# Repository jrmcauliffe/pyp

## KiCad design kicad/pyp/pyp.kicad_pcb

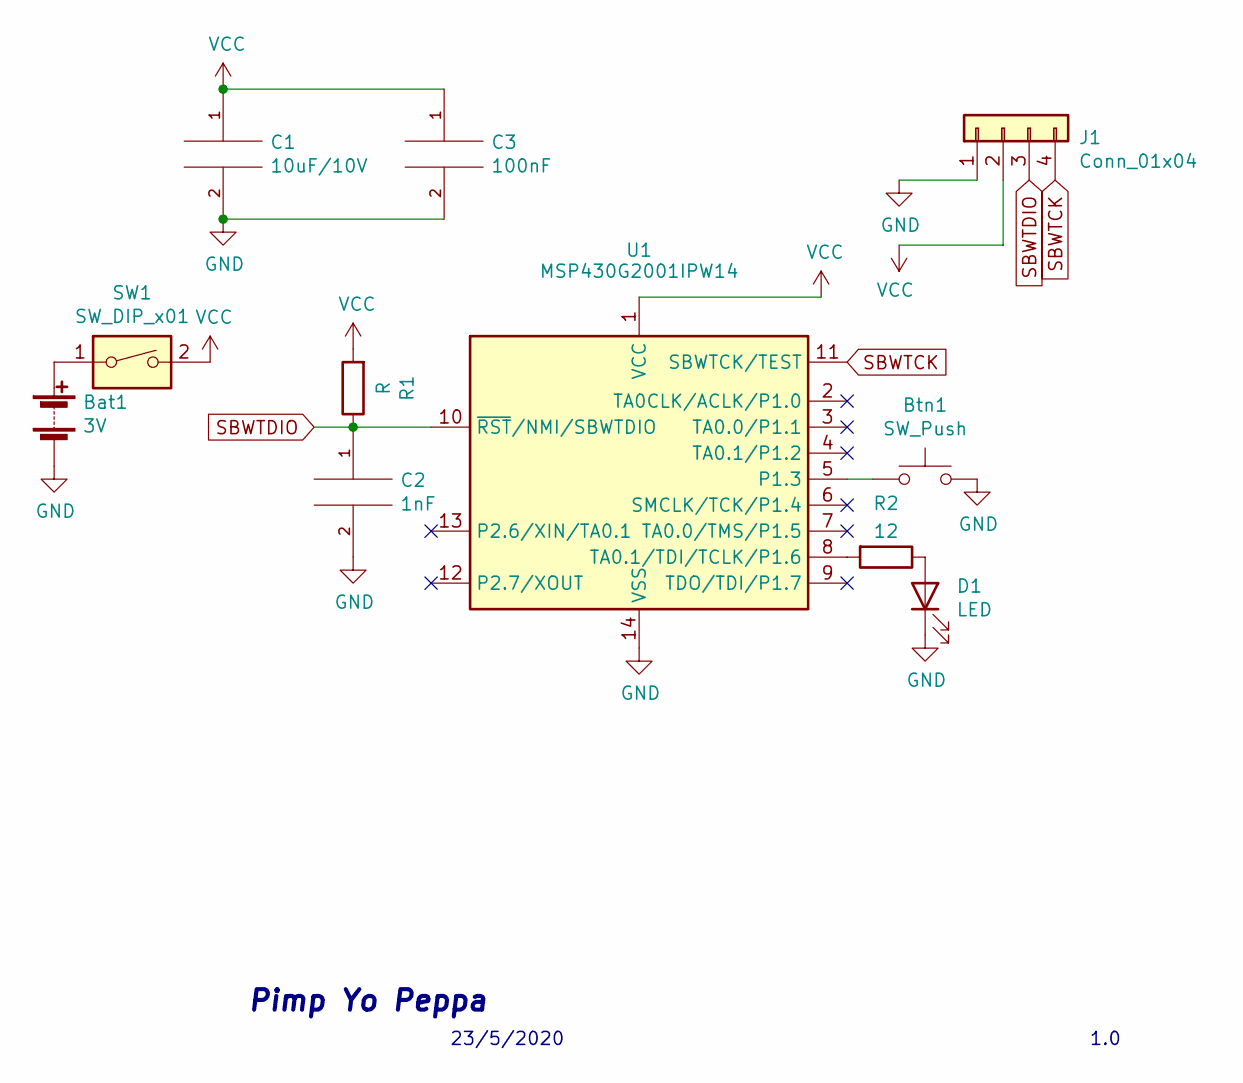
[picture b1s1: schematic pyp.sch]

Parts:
Bat1: 3V; SolderWire-0.1sqmm_1x02_P3.6mm_D0.4mm_OD1mm
Btn1: SW_Push; SolderWire-0.1sqmm_1x02_P3.6mm_D0.4mm_OD1mm
C1: 10uF/10V; C_0603_1608Metric_Pad1.05x0.95mm_HandSolder
C2: 1nF; C_0603_1608Metric_Pad1.05x0.95mm_HandSolder
C3: 100nF; C_0603_1608Metric_Pad1.05x0.95mm_HandSolder
D1: LED; SolderWire-0.1sqmm_1x02_P3.6mm_D0.4mm_OD1mm
J1: Conn_01x04; PinHeader_1x04_P2.54mm_Vertical
R1: R; R_0603_1608Metric_Pad1.05x0.95mm_HandSolder
R2: 12; R_Axial_DIN0207_L6.3mm_D2.5mm_P7.62mm_Horizontal
SW1: SW_DIP_x01; SolderWire-0.1sqmm_1x02_P3.6mm_D0.4mm_OD1mm
U1: MSP430G2001IPW14; TSSOP-14_4.4x5mm_P0.65mm

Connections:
GND: Bat1.2 (-), Btn1.2, C1.2, C2.2, C3.2, D1.1 (K), J1.1, U1.14 (VSS)
unnamed: Bat1.1 (+), SW1.1
unnamed: Btn1.1, U1.5 (P1.3)
unnamed: D1.2 (A), R2.1
unnamed: R2.2, U1.8 (TA0.1/TDI/TCLK/P1.6)
SBWTCK: J1.4, U1.11 (SBWTCK/TEST)
SBWTDIO: C2.1, J1.3, R1.1, U1.10 (~RST~/NMI/SBWTDIO)
VCC: C1.1, C3.1, J1.2, R1.2, SW1.2, U1.1 (VCC)

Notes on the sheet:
23/5/2020
1.0
Pimp Yo Peppa

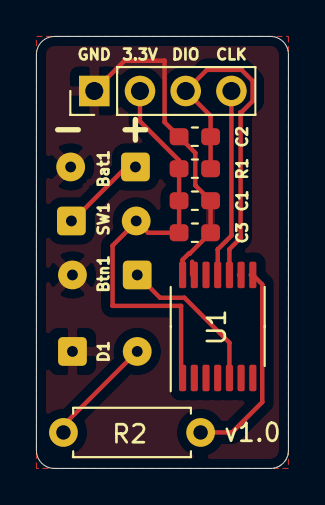
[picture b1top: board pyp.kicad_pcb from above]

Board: 2 copper layers, 14.0 x 24.0 mm, 11 parts (0 on the bottom side), 8 nets.

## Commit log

2020-05-22 PCB v1.0
2020-05-22 Fix renaming issue
2020-05-24 v1.0
2020-05-26 Blinky inital firmware
2020-05-28 Remove Old config
2020-05-28 Updated project
2020-05-28 Basic gamma step through
2020-05-30 Basic debounced switch
2020-05-30 WIP Shutdown Timer
2020-05-30 WIP working brightness cycle logic
2020-05-30 Working sleep with simple fade out
2020-05-30 Formatting
2020-06-01 Scale timer constants for 1Khz operation
2020-06-01 Unix line endings
2020-06-01 Use correct constants for Timer configuration
2020-06-01 Comments and refactor
2020-06-01 Fix timeout
2020-06-01 Tweak debounce timing
